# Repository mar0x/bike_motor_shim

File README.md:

# Shimano e-bike motor shim
Shimano e-bike shim between wheel sensor and motor to "extend the limits".

Attiny85 controller reads sensor pulses and adjust frequency to keep assist working.
Shim has relay for by-pass which is activated in absence of power. Most expensive part
is Shimano Di2 wire and Junction required for smooth connection.

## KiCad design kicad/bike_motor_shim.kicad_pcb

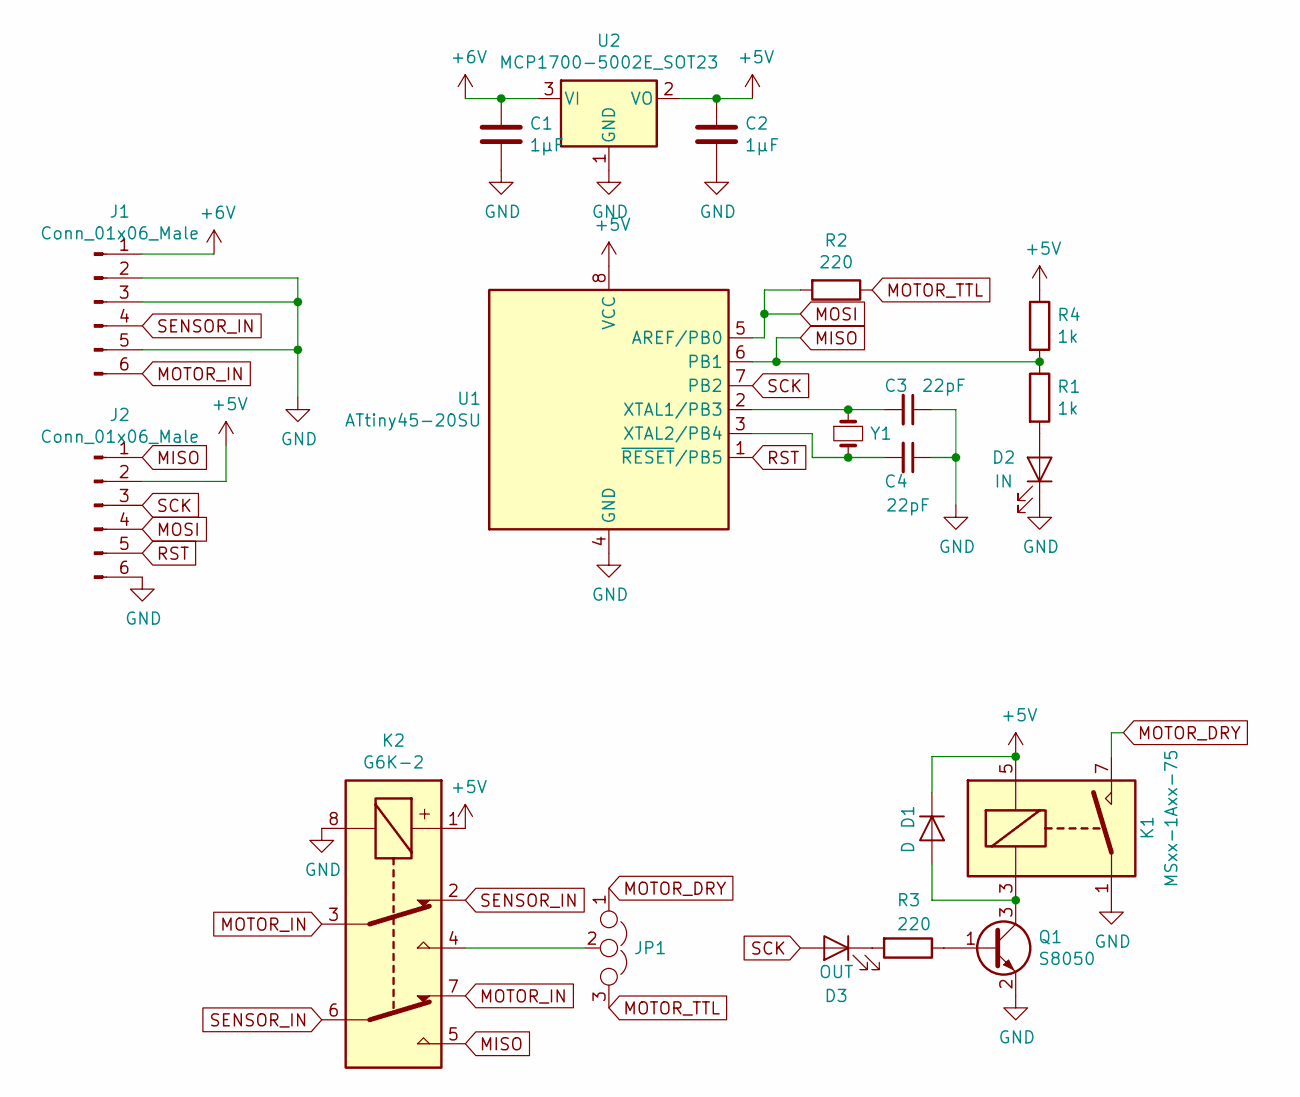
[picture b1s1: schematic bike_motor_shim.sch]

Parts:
C1, C2: 1µF; C_0805_2012Metric_Pad1.15x1.40mm_HandSolder
C3, C4: 22pF; C_0805_2012Metric_Pad1.15x1.40mm_HandSolder
D1: D; D_SMA
D2: IN; LED_0805_2012Metric_Pad1.15x1.40mm_HandSolder
D3: OUT; LED_0805_2012Metric_Pad1.15x1.40mm_HandSolder
J1, J2: Conn_01x06_Male; JST_XH_S06B-XH-A-1_1x06_P2.50mm_Horizontal
JP1: Jumper_NC_Dual; PinHeader_1x03_P2.54mm_Vertical
K1: MSxx-1Axx-75; Relay_SPST_StandexMeder_SIL_Form1A
K2: G6K-2; Relay_DPDT_Omron_G6K-2F-Y
Q1: S8050; SOT-23
R1, R4: 1k; R_0805_2012Metric_Pad1.15x1.40mm_HandSolder
R2, R3: 220; R_0805_2012Metric_Pad1.15x1.40mm_HandSolder
U1: ATtiny45-20SU; SOIJ-8_5.3x5.3mm_P1.27mm
U2: MCP1700-5002E_SOT23; SOT-23
Y1: Crystal_Small; Crystal_HC49-4H_Vertical

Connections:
+5V: C2.1, D1.1 (K), J2.2, K1.5, K2.1, R4.1, U1.8 (VCC), U2.2 (VO)
+6V: C1.1, J1.1, U2.3 (VI)
GND: C1.2, C2.2, C3.1, C4.1, D2.1 (K), J1.2, J1.3, J1.5, J2.6, K1.1, K2.8, Q1.2 (E), U1.4 (GND), U2.1 (GND)
MISO: J2.1, K2.5, R1.1, R4.2, U1.6 (PB1)
MOSI: J2.4, R2.2, U1.5 (AREF/PB0)
MOTOR_DRY: JP1.1, K1.7
MOTOR_IN: J1.6, K2.3, K2.7
MOTOR_TTL: JP1.3, R2.1
unnamed: C3.2, U1.2 (XTAL1/PB3), Y1.1
unnamed: C4.2, U1.3 (XTAL2/PB4), Y1.2
unnamed: D1.2 (A), K1.3, Q1.3 (C)
unnamed: D2.2 (A), R1.2
unnamed: D3.1 (K), R3.2
unnamed: JP1.2, K2.4
unnamed: Q1.1 (B), R3.1
RST: J2.5, U1.1 (~RESET~/PB5)
SCK: D3.2 (A), J2.3, U1.7 (PB2)
SENSOR_IN: J1.4, K2.2, K2.6

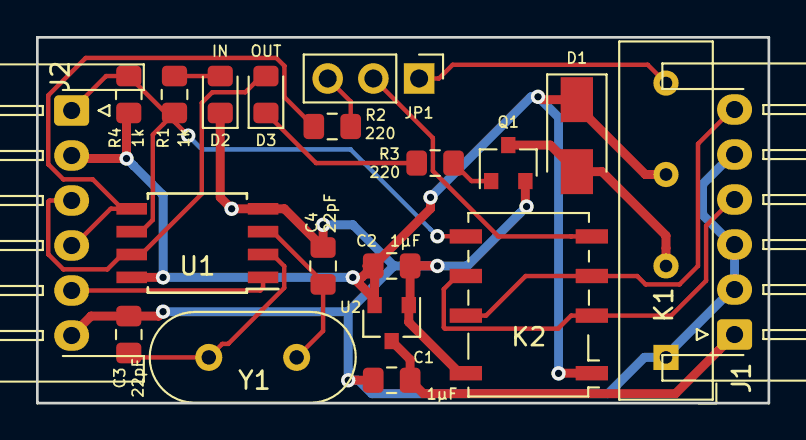
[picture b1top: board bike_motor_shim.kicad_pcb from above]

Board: 2 copper layers, 40.6 x 20.3 mm, 20 parts (0 on the bottom side), 18 nets.

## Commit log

2019-06-28 PCB prototype
2019-06-28 Fixed relay footprint
2019-06-28 Improving frequency limit.
2019-06-28 Fixing relay on/off conditions
2019-06-28 Using button debouncer.
2019-07-07 Adding bypass relay and LEDs.
2019-07-26 Fixing traces.
    Adding missed trace and increasing width of ground and power traces.
2019-07-26 Adapting code for updated board.
    Sensor on is externally pulled-up, sensor out transformed to experimental
    TTL output.
2019-08-10 Board and sketch improvements.
2019-09-11 Adjusting debouncer and fixing pulse width reset.
2019-10-31 Adding dimensions.
2019-10-31 Adding rendered image and README file.
2019-11-01 Removing generated file.
2019-11-01 Using env. variables instead of full path.
2019-11-01 Adding .gitignore.
